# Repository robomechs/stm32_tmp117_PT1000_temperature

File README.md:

# STM32F103C8 BluePill USB Temperature Monitor

This project is a USB-connected temperature measurement setup for the STM32F103C8T6 **BluePill** board.

It combines:

- a **PT1000** analog sensor read by the STM32 ADC,
- a **TMP117** digital sensor connected over I2C,
- direct **USB CDC** communication from the BluePill to the PC,
- and a desktop **Python viewer** for live plotting, software filtering, and CSV logging.

The board connects to the PC **directly over USB** and enumerates as a virtual COM port. No separate USB-UART adapter is required.

## Project Overview

The firmware runs on an STM32F103C8-based BluePill board and streams temperature data over USB CDC.

Current default behavior:

- **PT1000** is sampled through the ADC at **1 kHz**
- the PT1000 ADC path is smoothed in firmware with a fixed-point LPF at about **10 Hz**
- PT1000 temperature is transmitted over USB at **20 Hz**
- **TMP117** is still polled in firmware at **20 Hz**
- TMP117 is **not filtered in firmware**
- TMP117 is **not sent by default**, but the code already supports switching to TMP117-only or both-sensors output

On the PC side, the included viewer can:

- connect to the USB virtual COM port,
- display live values,
- plot incoming data,
- apply a **software LPF** in the GUI,
- show or hide raw and filtered traces independently,
- and log data to CSV.

## Hardware

### Target MCU board

- **STM32F103C8T6 BluePill**

## Measurement Ranges

Reference specifications used here:

- [PT106052 / SA10200542 PT1000 listing](https://www.tme.com/ca/en/details/pt106052/temp-sensors-resistance-thermometers/cyntec-co-ltd/sa10200542/)
- [TI TMP117 product page](https://www.ti.com/product/TMP117)

### PT1000 channel

The PT1000 element used for this project is PT106052 / SA10200542 style: `Pt1000`, class B `0.12 %`, `3850 ppm/C`, with a specified operating range of approximately **-50 C to +500 C**.

This is the intended practical measurement range for the PT1000 channel.

The firmware uses a simple linear PT1000 approximation:

```text
R(T) = R0 * (1 + 0.00385 * T)
```

So the conversion is intentionally simple and integer-friendly for STM32F103. For better absolute accuracy across the full `-50...500 C` span, the next improvement would be a calibrated table or Callendar-Van Dusen conversion.

With the current divider value, the PT1000 range maps well into the 12-bit ADC input range:

| Temperature | Approx. PT1000 resistance | Approx. ADC code | Approx. ADC voltage at 3.3 V |
| --- | ---: | ---: | ---: |
| `-50 C` | `807.5 Ohm` | `2749` | `2.22 V` |
| `0 C` | `1000.0 Ohm` | `2550` | `2.06 V` |
| `25 C` | `1096.3 Ohm` | `2460` | `1.98 V` |
| `100 C` | `1385.0 Ohm` | `2226` | `1.79 V` |
| `500 C` | `2925.0 Ohm` | `1477` | `1.19 V` |

The ADC itself has much wider mathematical headroom, but the useful documented PT1000 range should be treated as **-50 C to +500 C** unless the sensor, mounting, wiring, and calibration are validated outside that range.

### TMP117 channel

The TMP117 channel is intended for the TMP117 operating range: **-55 C to +150 C**.

In the current firmware, TMP117 is polled at `20 Hz`, but the default USB stream sends PT1000 only. TMP117 output can be enabled in firmware with `USB_STREAM_MODE_TMP117` or `USB_STREAM_MODE_BOTH`.

### PT1000 connection

The PT1000 is connected as a simple divider from `3.3 V`:

- top resistor: **PT1000**
- bottom resistor: **1.65 kOhm**
- divider midpoint: `PA0 / ADC1_IN0`

Divider:

`3.3V -> PT1000 -> PA0 -> 1.65k -> GND`

The `1.65 kOhm` resistor was chosen to place the expected `-50...500 C` PT1000 resistance range comfortably inside the ADC range while keeping useful sensitivity over the whole span. It is not a common single resistor value, so it can be made from **two 3.3 kOhm resistors in parallel**:

```text
3.3k || 3.3k = 1.65k
```

The divider resistor is used directly by the firmware conversion. In [main.c](TMP117_stm32f103c8/Core/Src/main.c), the value is defined as `PT1000_BOTTOM_RESISTOR_MOHM`. It is stored in milliohms; the current nominal value is `1650000`, meaning `1650.000 Ohm`.

If better absolute accuracy is needed, measure the actual parallel resistance and put that value into `PT1000_BOTTOM_RESISTOR_MOHM` in milliohms.

If the PT1000 and the `1.65 kOhm` resistor are physically swapped during assembly, the firmware can be switched without rewiring. Set `PT1000_DIVIDER_PT1000_ON_TOP` to `0` in [main.c](TMP117_stm32f103c8/Core/Src/main.c). Default is `1`, meaning `3.3V -> PT1000 -> PA0 -> 1.65k -> GND`.

Swapping the divider mostly reverses the ADC slope. Sensitivity and self-heating are nearly the same because the same two resistors are still in series. With the correct define, measurements remain valid; with the wrong define, the temperature will be badly wrong.

### TMP117 connection

- `PB6` -> `I2C1_SCL`
- `PB7` -> `I2C1_SDA`
- default I2C address: `0x48`

Additional pins:

- `PB8` -> TMP117 `ALERT` input with external pull-up
- `PB9` -> TMP117 `ADD0` output, held low with external pull-down

### USB connection

The firmware uses the STM32 USB CDC device interface and appears on the PC as a virtual COM port.

Project-specific USB notes:

- `PB5` is used for the external USB reconnect/reset wiring
- D+ has an external `1.5 kOhm` pull-up to `3.3 V`
- the firmware generates a reconnect pulse during startup so the BluePill re-enumerates cleanly over USB

## Firmware

Firmware source is in:

- [TMP117_stm32f103c8](TMP117_stm32f103c8)

Main application file:

- [main.c](TMP117_stm32f103c8/Core/Src/main.c)

### Firmware data path

#### PT1000 path

- sampled by `ADC1` on `PA0`
- ADC timing tuned for slower, quieter sampling
- sampled at **1 kHz**
- filtered in firmware with fixed-point arithmetic
- converted to temperature in degrees Celsius
- sent over USB at **20 Hz**

#### TMP117 path

- read over `I2C1`
- polled at **20 Hz**
- kept in firmware for reference / comparison
- **not filtered in firmware**
- **not streamed by default**

### Default USB output

Current default build sends only PT1000:

```text
PT1000=24.875 C
```

With line ending on the wire:

```text
PT1000=24.875 C\r\n
```

### Other firmware output modes

The firmware can also send:

- TMP117 only
- both PT1000 and TMP117 in one line

These modes are selected in [main.c](TMP117_stm32f103c8/Core/Src/main.c) by the `USB_STREAM_MODE` define.

Typical options in the code:

- `USB_STREAM_MODE_PT1000`
- `USB_STREAM_MODE_TMP117`
- `USB_STREAM_MODE_BOTH`

Example combined line:

```text
PT1000=24.875 C TMP117=24.937 C
```

## Desktop Viewer

Viewer file:

- [temperature_viewer.pyw](temperature_viewer.pyw)

The viewer is intended for direct use with the BluePill USB CDC connection.

### Viewer features

- automatic COM port refresh
- connect/disconnect control
- compact COM names such as `COM3`
- live readout for PT1000 and TMP117
- plot view for one sensor or both sensors
- separate **Show raw** and **Show filtered** checkboxes
- software LPF modes:
  - `Off`
  - `EMA`
  - `SMA`
- adjustable visible X-axis window
- `Follow latest` mode
- `Auto Y`
- `Show all`
- `Reset view`
- `Clear plot`
- `Help` button with built-in usage notes
- CSV logging

### Important note about filtering

There are two different filtering layers in this project:

1. **Firmware PT1000 LPF**
   - applied on the MCU to the ADC path
   - fixed-point
   - currently about `10 Hz`

2. **Viewer software LPF**
   - applied inside the PC application
   - tunable in the UI
   - available for display, comparison, and CSV logging

TMP117 currently has **no firmware LPF**. In the viewer, TMP117 can still be filtered in software for visualization.

### Viewer input formats

The viewer accepts the current labeled firmware stream, for example:

```text
PT1000=24.875 C
```

or:

```text
PT1000=24.875 C TMP117=24.937 C
```

It also keeps compatibility with older single-value lines through the `Single line` selector in the UI.

### CSV logging

The viewer can save CSV with these columns:

```text
timestamp_s,pt1000_raw_c,pt1000_filtered_c,tmp117_raw_c,tmp117_filtered_c
```

## Python Requirements

The viewer uses:

- Python 3
- `PyQt6`
- `pyqtgraph`
- `pyserial`

Example install command:

```bash
pip install PyQt6 pyqtgraph pyserial
```

Run the viewer with:

```bash
py temperature_viewer.pyw
```

On Windows, you can also launch the `.pyw` file directly.

## Building the Firmware

This firmware project is based on an STM32CubeIDE-generated STM32F103 project.

Main project file:

- [TMP117_stm32f103c8.ioc](TMP117_stm32f103c8/TMP117_stm32f103c8.ioc)

### Recommended build flow

1. Open the project in **STM32CubeIDE**
2. Open the `.ioc` if needed
3. Let CubeIDE regenerate project files if required
4. Build the project for the **STM32F103C8T6 BluePill**
5. Flash it with your usual ST-Link workflow

### Command-line build

If the local `Debug` build directory already exists, the project can also be built with:

```bash
make -C TMP117_stm32f103c8/Debug all
```

Note:

- `Debug/` is gitignored
- in a fresh clone, it is normal to open the project in CubeIDE first so the build files are present locally

## Repository Layout

- [TMP117_stm32f103c8](TMP117_stm32f103c8) - STM32 firmware project
- [temperature_viewer.pyw](temperature_viewer.pyw) - desktop GUI viewer
- [TMP117_PCB](TMP117_PCB) - KiCad PCB project

Inside the PCB folder:

- KiCad source project is in [tmp117](TMP117_PCB/tmp117)
- [bom](TMP117_PCB/tmp117/bom) contains BOM-related output
- [manuf](TMP117_PCB/tmp117/manuf) contains manufacturing files

## Practical Usage

Typical workflow:

1. Flash the firmware to the **BluePill**
2. Connect the board to the PC via **USB**
3. Wait for the USB CDC virtual COM port to appear
4. Start [temperature_viewer.pyw](temperature_viewer.pyw)
5. Select the COM port
6. Click `Connect`
7. View live temperature, tune software LPF, and log CSV if needed

## Notes

- The repository ignores generated build outputs, Python cache files, KiCad local history, and KiCad backup archives.
- The current default USB stream is PT1000-only, which keeps the USB output simple for the viewer and logging workflow.
- TMP117 acquisition is still active in firmware, so enabling dual-sensor output later is straightforward.

## PT1000 Wiring Quick Reference

Use this connection for the PT1000 divider:

```text
BluePill 3V3 -> PT1000 -> PA0 / ADC1_IN0 -> 1.65k -> GND
```

This is the default firmware setting:

```c
#define PT1000_DIVIDER_PT1000_ON_TOP 1U
```

If the parts are swapped:

```text
BluePill 3V3 -> 1.65k -> PA0 / ADC1_IN0 -> PT1000 -> GND
```

use this firmware setting:

```c
#define PT1000_DIVIDER_PT1000_ON_TOP 0U
```

The bottom resistor may be either:

```text
single 1.65k resistor
```

or:

```text
two 3.3k resistors in parallel
```

Keep the ADC node connected only to `PA0`, the PT1000, and the bottom resistor. Do not connect the divider to `5 V`; the firmware assumes `3.3 V` ADC reference behavior.

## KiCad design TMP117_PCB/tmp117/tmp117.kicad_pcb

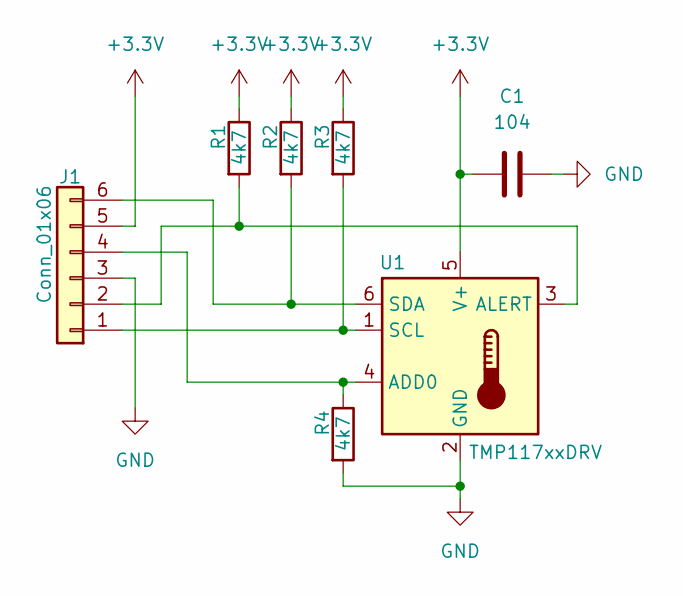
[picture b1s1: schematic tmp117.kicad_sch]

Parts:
C1: 104; C_1206_3216Metric
J1: Conn_01x06; Zhaoxing_VH_ZX-VH3.96-6PLT_1x06-1MP_P3.96mm_Vertical
R1, R2, R3, R4: 4k7; R_0805_2012Metric_Pad1.20x1.40mm_HandSolder
U1: TMP117xxDRV; WSON-6-1EP_2x2mm_P0.65mm_EP1x1.6mm

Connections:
+3.3V: C1.1, J1.5, R1.1, R2.1, R3.1, U1.5 (V+)
GND: C1.2, J1.3, R4.2, U1.2 (GND)
unnamed: J1.1, R3.2, U1.1 (SCL)
unnamed: J1.2, R1.2, U1.3 (ALERT)
unnamed: J1.4, R4.1, U1.4 (ADD0)
unnamed: J1.6, R2.2, U1.6 (SDA)

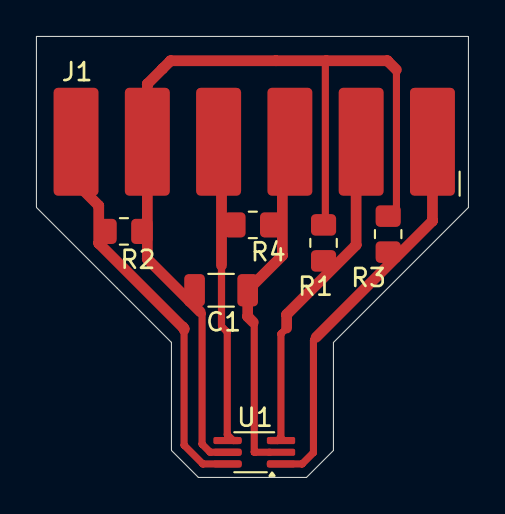
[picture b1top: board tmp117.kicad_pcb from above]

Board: 2 copper layers, 24.0 x 24.5 mm, 7 parts (0 on the bottom side), 6 nets.

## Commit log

2026-03-25 Add gitignore and remove generated artifacts
2026-03-25 readme added
2026-05-05 Document PT1000 range and nominal divider
2026-05-14 Add PT1000 divider orientation switch
